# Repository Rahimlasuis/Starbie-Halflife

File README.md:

<h1>Starbie</h1> <br>
<h1>Description</h1> <br>
Starbie is an interactive desktop companion built following a written hackclub guide on halflife. It is built using XIAO ESP32 as the microcontroller(the brain of the system).<br>
This project is not a complete replication of the guide as it includes some extra features including custom underglowing effects, light, alarm system and interactive features.
<h1>About the Process</h1> <br>
This is my very first hardware project.
i followed the starbie guide on halflife.
building some kind of desktop companion
i started by bringing in components , symbols and power symbols in the schematic.
then i wired them up according to the guide.
i updated the pcb
traced the edges
routed the pcb
run DHR
ignored the errors lol
added some components of my own
opened arduino ide
installed all the things i was askd to install by the guide.
pasted the code
edited the code to work with my components
troublshooted
cried
tears
compiling errors, so many times, i think due to repeated lines of the same code
it finally wokrked <br>

<h1>Additional Features explained</h1>
1. Passive Buzzer: It gives Starbie sound. It generates beeping sound effects when it is turned on. Also when emmits sound when buttons and keys are physically used
<br>
2. Light Sensor: Monitors the surrounding light levels using voltage divider circuit. 
When the surrounding seems dark it should automatically switch to sleep mode
<br>
3. RGB Leds: Provides underglow effect to the starbie depending on the current situation. green on successful booting and others
<br>
google was my friend all the way.
and it also gave me lot of work.
never let AI write codes for you.

I also suffered a lot because of my system. It was so slow and at some point i lost unsaved changes. I cried lol
<br>
<h3>here are some images too</h3>

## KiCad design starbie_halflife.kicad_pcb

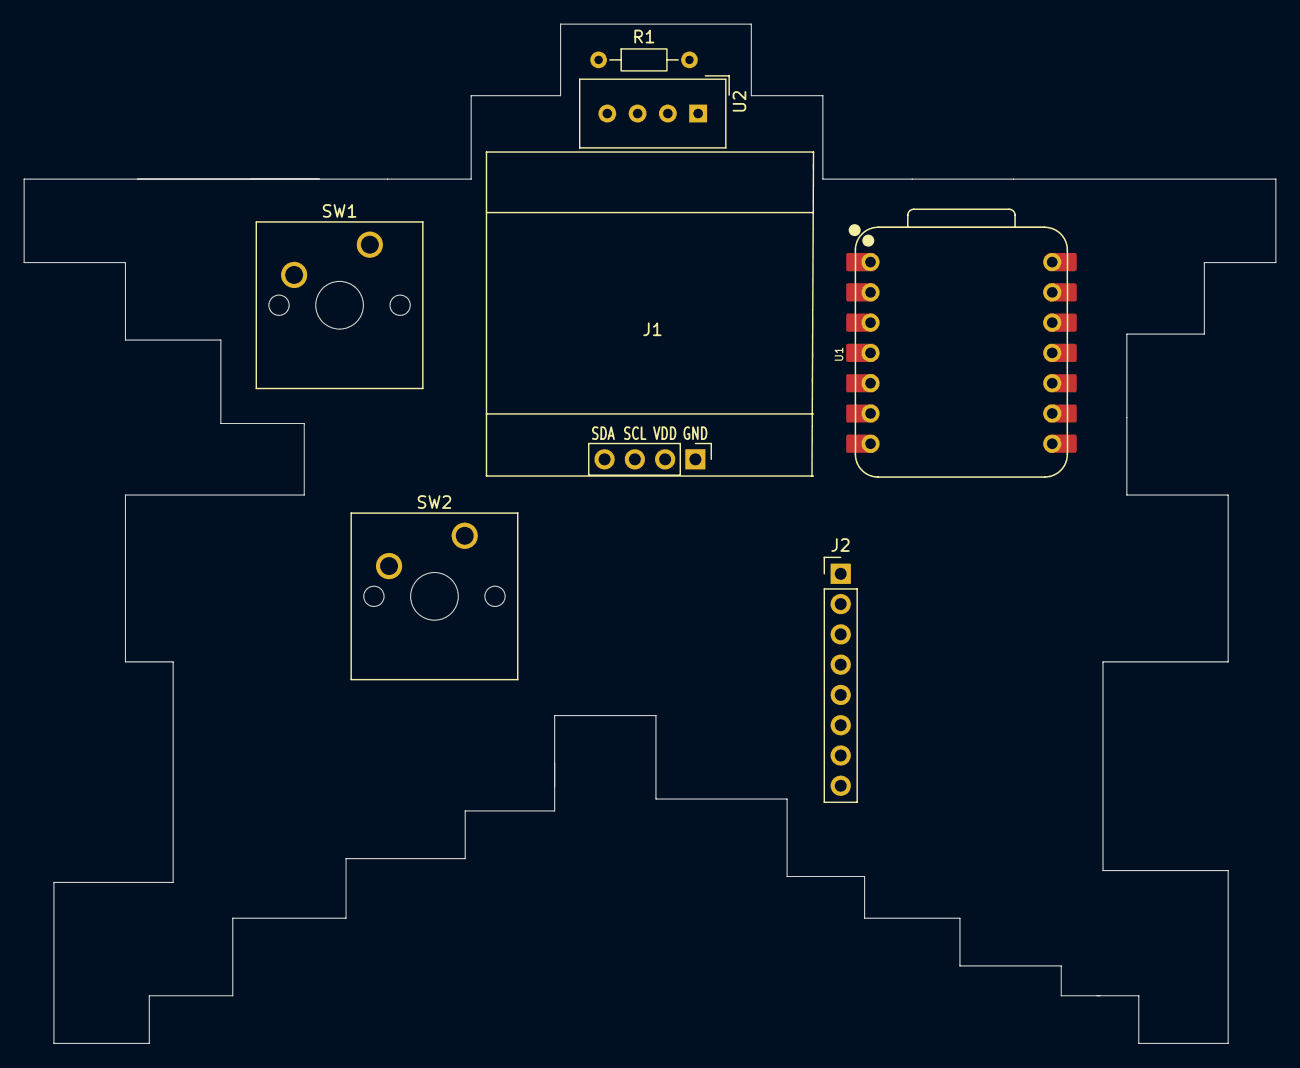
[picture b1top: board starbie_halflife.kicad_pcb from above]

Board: 2 copper layers, 105.0 x 85.5 mm, 7 parts (0 on the bottom side), 3 nets, no tracks yet.

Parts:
J1: Conn_01x04_Pin; Display_128x64_096_I2C
J2: Conn_01x08_Pin; PinHeader_1x08_P2.54mm_Vertical
R1: R; R_Axial_DIN0204_L3.6mm_D1.6mm_P7.62mm_Horizontal
SW1, SW2: SW_Push; SW_Cherry_MX_1.00u_PCB
U1: XIAO-ESP32-C3-SMD; XIAO-ESP32-C6-DIP
U2: DHT11; Aosong_DHT11_5.5x12.0_P2.54mm

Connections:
+3.3V: J1.2, J2.1, R1.1, U1.12 (3V3_OUT), U2.1 (VDD)
/DHT11 DATA: R1.2, U2.2 (DATA)
GND: J1.1, J2.2, SW1.2, SW2.2, U1.13 (GND), U2.4 (GND)

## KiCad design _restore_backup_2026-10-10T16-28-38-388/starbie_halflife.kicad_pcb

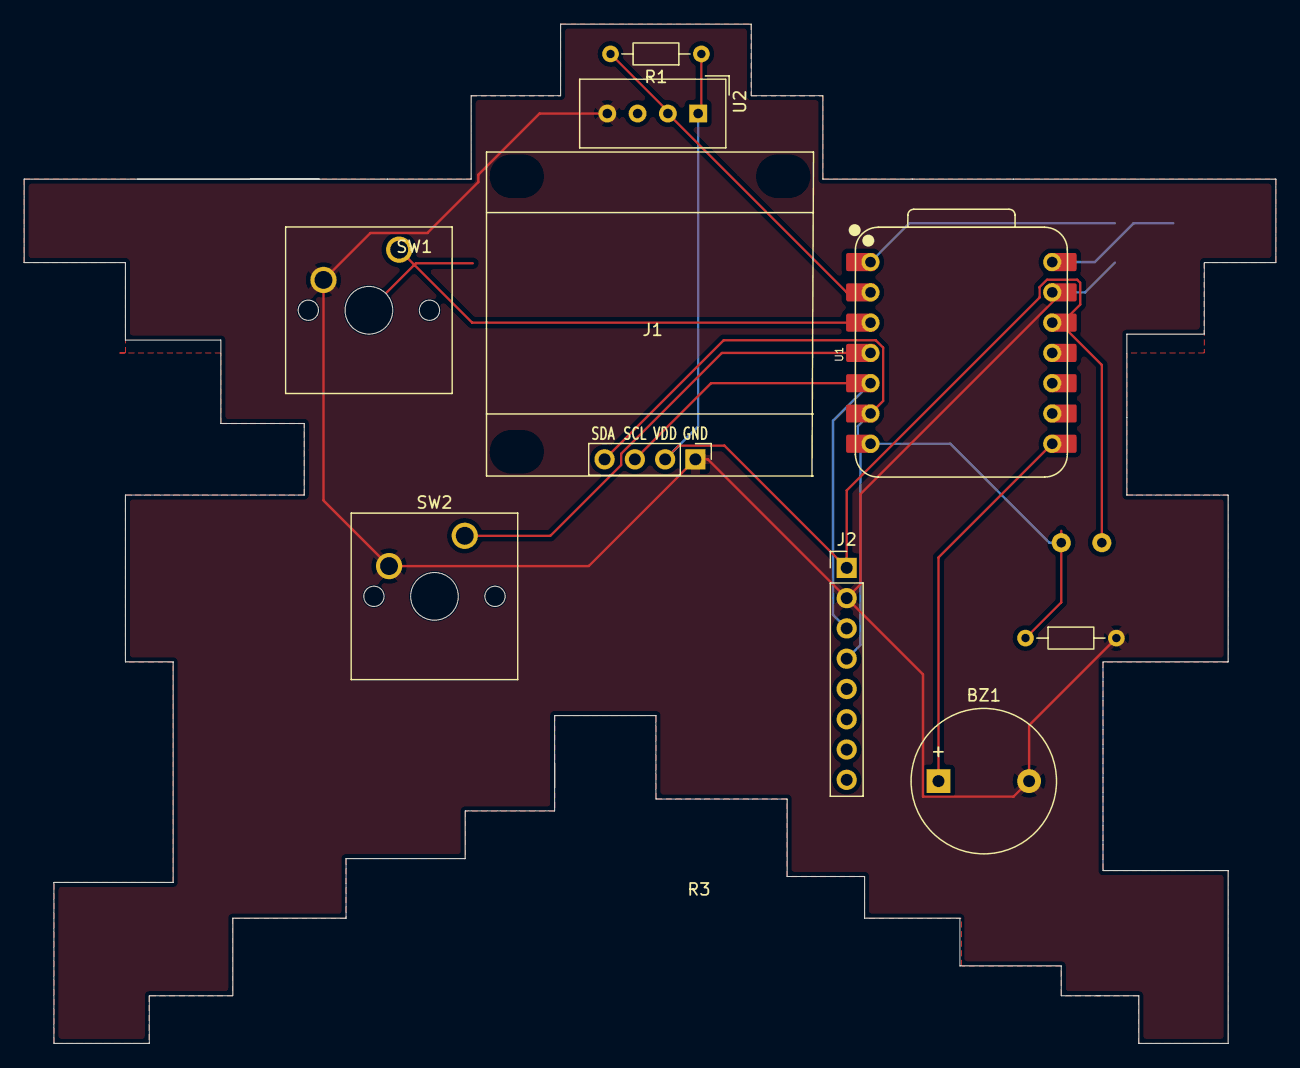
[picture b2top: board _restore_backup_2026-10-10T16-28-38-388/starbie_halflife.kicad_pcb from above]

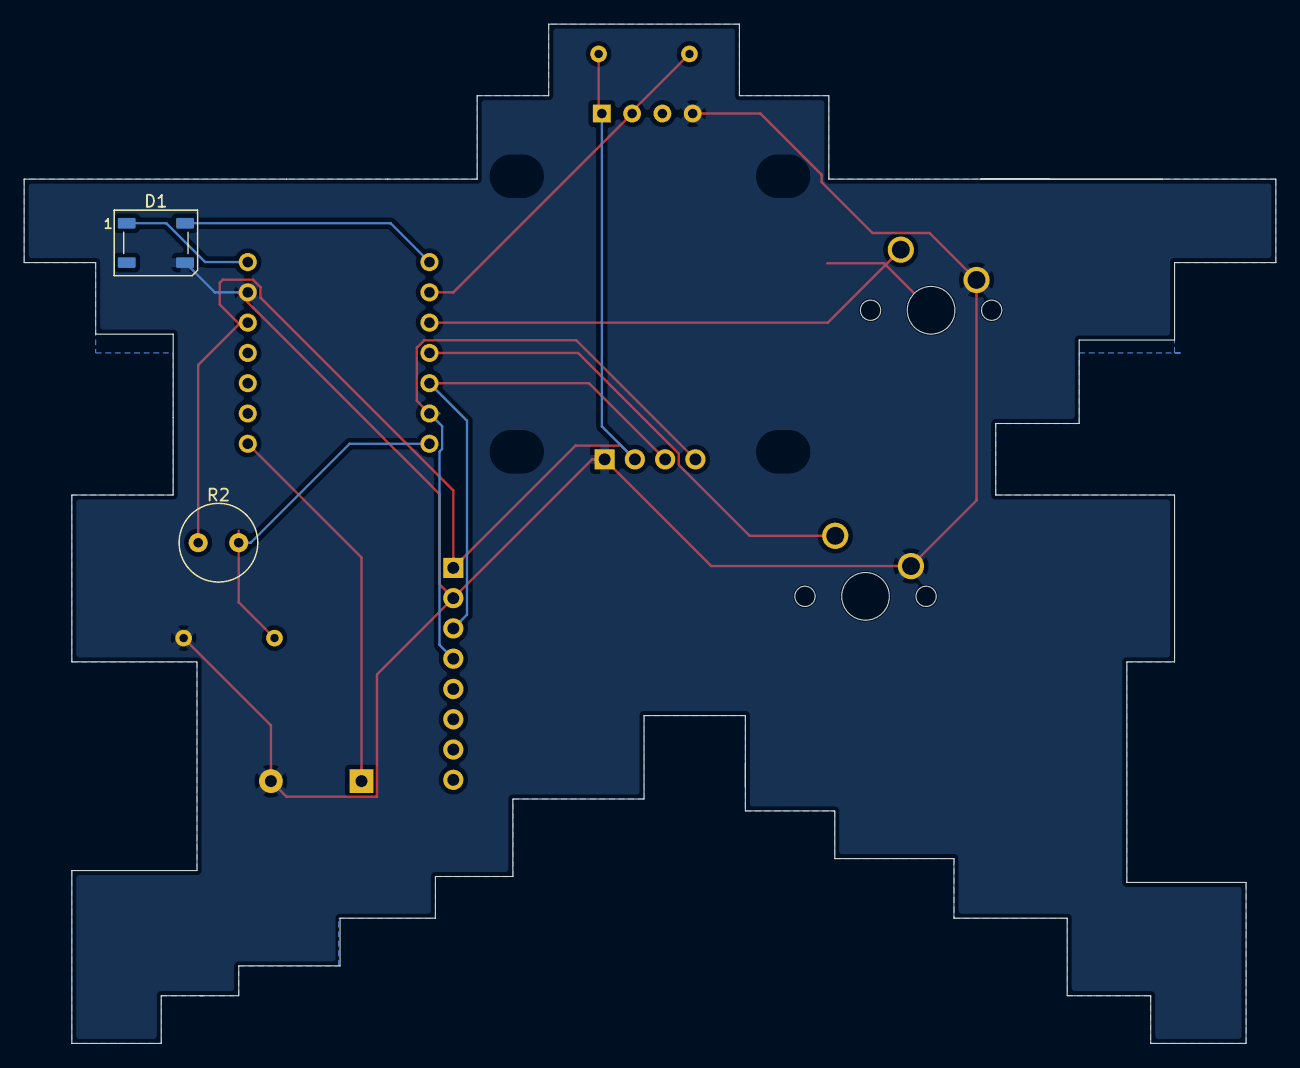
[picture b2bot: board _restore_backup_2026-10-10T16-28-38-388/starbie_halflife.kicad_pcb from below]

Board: 2 copper layers, 105.0 x 85.5 mm, 11 parts (2 on the bottom side), 11 nets.

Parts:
BZ1: Buzzer; Buzzer_12x9.5RM7.6
D1: WS2812B; LED_WS2812B_PLCC4_5.0x5.0mm_P3.2mm
J1: Conn_01x04_Pin; Display_128x64_096_I2C
J2: Conn_01x08_Pin; PinHeader_1x08_P2.54mm_Vertical
R1, R3: R; R_Axial_DIN0204_L3.6mm_D1.6mm_P7.62mm_Horizontal
R2: A1050; R_LDR_D6.4mm_P3.4mm_Vertical
SW1, SW2: SW_Push; SW_Cherry_MX_1.00u_PCB
U1: XIAO-ESP32-C3-SMD; XIAO-ESP32-C6-DIP
U2: DHT11; Aosong_DHT11_5.5x12.0_P2.54mm

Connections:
+3.3V: J1.2, J2.1, R1.1, R2.1, U1.12 (3V3_OUT), U2.1 (VDD)
+5V: D1.1 (VDD), U1.14 (VBUS)
/DHT11 DATA: R1.2, U1.2 (D1), U2.2 (DATA)
/GPIO2: SW1.1, U1.3 (D2)
/GPIO3: SW2.1, U1.4 (D3)
/SCL: J1.3, J2.3, U1.5 (D4)
/SDA: J1.4, J2.4, U1.6 (D5)
GND: BZ1.2 (-), D1.3 (VSS), J1.1, J2.2, R3.2, SW1.2, SW2.2, U1.13 (GND), U2.4 (GND)
unnamed: BZ1.1 (+), U1.8 (D7)
unnamed: D1.4 (DIN), U1.1 (D0)
unnamed: R2.2, R3.1, U1.7 (D6)
